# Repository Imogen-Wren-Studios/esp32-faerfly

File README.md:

#ESP32 FaerFly - Development Board
 Imogen Wren Business Card PCB

## Project Outline

_The project is a business card that can be handed out at gigs and work, and also a fun project to build!_

### Requirements
 1. A PCB business card I can hand out to people at gigs / work to advertise myself
 2. A fun electronics project or thing

### Idea

1. Mini pocket lightshow. Rechargable and interactive. Probably get it fabbed so it isnt a soldering project, but include a programming port so it can be reprogrammed easily. <br>
     **Advantages:**
    - Fun programming challenge - Can link to repo with working code in case of bricking
    - Card more likely to be used in the open and interacted with over time
    - Would have to be handed out with everything attached
    - Could exclude battery and make a point of indicating to reuse broken disposible vape for battery. Recycling electronic waste! 

 ## Strech Features
 
 - NFC Tap phone to link to linktree?
 - Edge connectors could be used as both touch interface, and connection to other hardware. Generic port? Is this now a new form we are trying to invent for development boards?
 - 3d printed case for different functions, like exposed touch pins, 

 ## Circuit Snippets
 
 ### WS2821b LED Implementation
 
  <br>
https://cdn-shop.adafruit.com/datasheets/WS2812B.pdf
- Vdd = 3.5 - 5.6 
- Vinput = VDD +-0.5

 Battery can be unregulated direct to LEDs & regulated to microcontroller
Slot for 2nd regulator for powering with 2s? or KISS

I think KISS

### Charging IC and LOw Voltage Cutoff

https://www.mouser.co.uk/ProductDetail/Littelfuse/SMAJ350A?

## Research

### AtTiny85 Interface
**DrAzzy - ATtiny Obsessee**
_Jan '20post #2_
_If you use my core (board manager url in sig), there is a serial bootloader (use the (optiboot) board def).
But you will still need an ISP programmer or arduino running Arduino as ISP sketch to bootload it (usbasps and nano clones are both 3 bucks or so on ebay/aliexpress, either is suitable).
You will also need a 0.1uf cap and 10k resistor for the autoreset circuit so the serial adapter can reset it into the bootloader. (Also, dont forget that you also need a 0.1uf ceramic cap between power and ground close to the t85 ti ensure reliable operation; without this the chip may behave erratically depending on circumstances - I mention this because it is very often omitted in designs I see here, particularly with tinies. You always need this for digital ICs unless otherwise specified in the datasheet. With the t85, if on breadboard or protoboard, i usually put this across the top of the chip to minimize the distance between cap and chip)_

#### USB - SPI Bridge

https://www.mouser.co.uk/ProductDetail/Microchip-Technology/MIC2550AYTS

#### USB C Connectors
https://www.mouser.co.uk/ProductDetail/Amphenol-Commercial-Products/124018402112A
https://www.lcsc.com/product-detail/span-style-background-color-ff0-USB-span-Connectors_G-Switch-GT-USB-7007A_C5299422.html

### LiPo Battery Charging
#### 1S
https://uk.rs-online.com/web/p/battery-management/7386360
https://www.mouser.co.uk/ProductDetail/Microchip-Technology-Atmel/MCP73832T-5ACI-OT
https://www.mouser.co.uk/datasheet/2/268/20001984g-846362.pdf

#### 2S
https://www.mouser.co.uk/ProductDetail/Microchip-Technology/MCP73844T-820I-MS

_This option needs regulator to 5v_

### Microcontroller Options
#### AtTiny85
- https://uk.farnell.com/microchip/attiny85-20su/mcu-8bit-attiny-20mhz-wsoic-8/dp/1455164
- Feels more "Haxxor" using a tiny processor
- More Difficult to implement
- The device achieves a throughput of 20 MIPS at 20 MHz and operates between 2.7 to 5.5V.
   - In voltage range 
- Have code almost ready to run https://github.com/Imogen-Wren-Studios/unicorn-attiny85

#### SAMD21
- 3.3v  MUST BE REGULATED
- Lots of experience with device
- https://www.mouser.co.uk/ProductDetail/Microchip-Technology/ATSAMD21E16L-AF?qs=9KdFJXLqUo%252B5fCZYsYcg9g%3D%3D

#### AtMega382p
- Most commonly understood platform - better engagement
- https://www.lcsc.com/product-detail/Microcontroller-Units-MCUs-MPUs-SOCs_Microchip-Tech-ATMEGA328P-AU_C14877.html
- Expensive
- in stock ATM
- 1.8 - 5.5v - No Need for Regulator
  - Qty.	Unit Price	Ext. Price
  - 1+	US  $3.045
  - 10+	US  $2.7126 - 	US$ 27.13

### ESP32
- 3v3 Only - needs regulating
- Wifiability gives further haxxor abilities
- OTA Updates
https://www.lcsc.com/product-detail/WiFi-Modules_Espressif-Systems-ESP32-WROOM-32-N4_C82899.html
- Have some code that could be used: https://github.com/Imogen-Wren-Studios/esp32-ws2812b-glediator
- Price: 
  - 1+   -  	US$3.2455	
  - 10+	 -   US$2.9273

### Capaciative Sensing

https://www.instructables.com/Capacitive-Sensing-for-Dummies/
_Seems to mostly be used with a microcontroller, havnt managed to find an analog audio implementation yet_

https://docs.arduino.cc/built-in-examples/analog/Smoothing Smoothing Data from Capacative touch sensor

## Continued Development

Now the project has become more clearly defined, it is an ESP development board with built in WS2821b LEDs designed to be used as a wearable badge, or a light up stand
for 3D printing projects. It contains mounting tabs to assit in adding diffusers and optics. The wifi can be used to coordinate groups of them to sync colours around the room.

## Version 2 Development

After using version 1 for a little time, some clear places to improve have materialised.

1.  [] Replace GPIO surface pins with through holes
2.  [] Replace USB to serial with CP2102, CH340 is too flakey see [CP2102 USB to UART](https://blackcatsoftware.us/wp-content/uploads/2020/06/esp32-devkit-v1-schematic.pdf)
3.  [] Add BMP280 temp sensor
4.  [] Add Accellerometer
5.  [] Add digital microphone? - test theory before committing
6.  [] DMX interface? -> `The DMX output required the use of a MAX485 transceiver connected to the TX-pin of the ESP in order to produce DMX output.` `If you need to use another pin for output than the TX-pin, you'll need to change this in the ESP-Dmx library itself. This setting is located in src/dependencies/dmx/ESPDMX.cpp on line 31.`
7.  [x] Battery Positive to ADC1 (GPIO32-39) with 100k resistor for battery usermod
8.  [x] Change Battery Switch to switch between USB and battery (why didnt do this on version 1?!?!)
9.  [x] Check max charge current for BMS. Need at least 1A if possible 550mA max using 2k ohm shunt resistor

Does DMX make this project something it is not?

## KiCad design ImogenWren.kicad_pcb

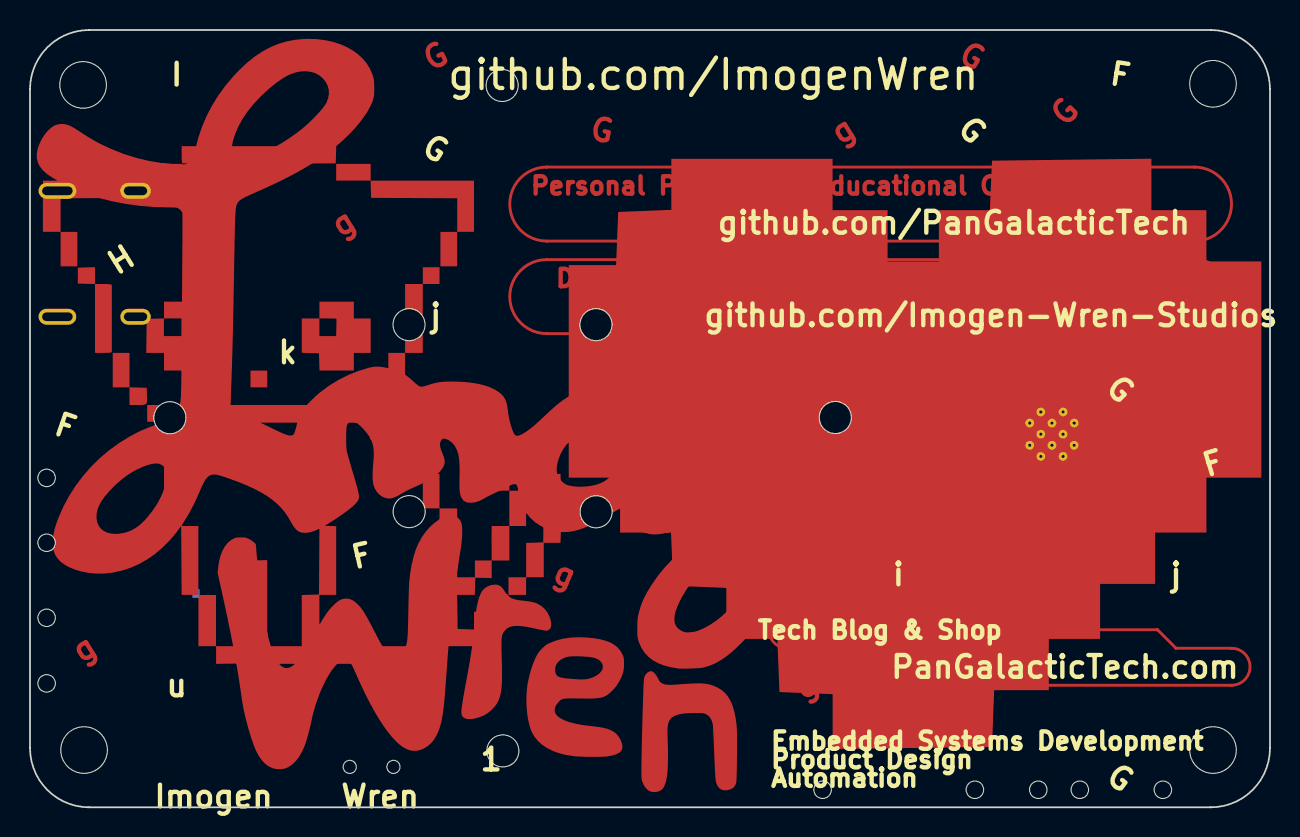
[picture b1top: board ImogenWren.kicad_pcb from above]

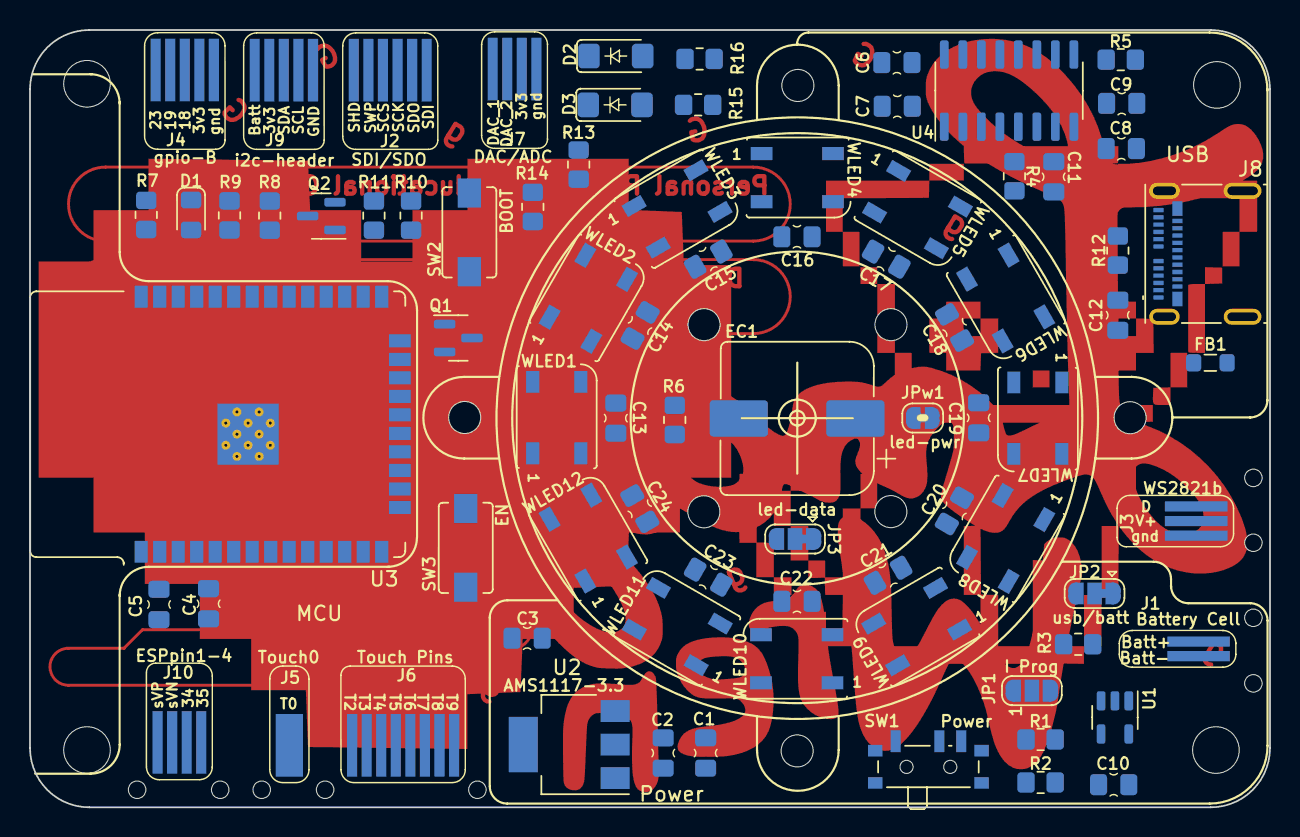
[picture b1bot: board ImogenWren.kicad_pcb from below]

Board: 2 copper layers, 85.1 x 53.3 mm, 80 parts (80 on the bottom side), 73 nets, no tracks yet.

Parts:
C1, C2, C3, C4, C5, C6, C7, C10, C13, C14, C15, C16, C17, C18, C19, C20, C21, C22, C23, C24: 100n; C_0805_2012_HandSolder_kawaii
C8: 10n; C_0805_2012_HandSolder_kawaii
C9, C11: 47p; C_0805_2012_HandSolder_kawaii
C12: 4n7; C_0805_2012_HandSolder_kawaii
D1: Blue; LED_0805_2012_Kawaii
D2, D3: BZV55B3V3; D_MiniMELF_kawaii
EC1: 1000u; CP_Elec_10x10_kawaii
FB1: FerriteBead; L_0805_2012Metric_Pad1.05x1.20mm_HandSolder
J1: Battery Cell; 2-pin-edge
J2: SDI/SDO; 6-pin-edge-touch
J3: WS2821b; 3-pin-edge
J4: gpio-B; 5-pin-edge-touch
J5: Touch0; 1-pin-edge-touch-xl
J6: Touch Pins; 8-pin-edge-touch
J7: DAC/ADC; 4-pin-edge
J8: USB_C_Receptacle; USB_C_Receptacle_Molex_105450-0101
J9: i2c-header; 5-pin-edge-touch
J10: ESPpin1-4; 4-pin-edge
JP1: I Prog; SolderJumper-3_P1.3mm_Open_RoundedPad1.0x1.5mm_NumberLabels
JP2: usb/batt; SolderJumper-3_P1.3mm_Bridged12_RoundedPad1.0x1.5mm
JP3: led-data; SolderJumper-3_P1.3mm_Bridged12_RoundedPad1.0x1.5mm
JPw1: led-pwr; SolderJumper-2_P1.3mm_Bridged_RoundedPad1.0x1.5mm
Q1, Q2: BC817; SOT-23
R1, R2, R8, R9, R10, R11: 10k; R_0805_2012Metric_Pad1.20x1.40mm_HandSolder
R3: 4k7; R_0805_2012Metric_Pad1.20x1.40mm_HandSolder
R4, R5: 27r; R_0805_2012Metric_Pad1.20x1.40mm_HandSolder
R6: 470r; R_0805_2012Metric_Pad1.20x1.40mm_HandSolder
R7: 330r; R_0805_2012Metric_Pad1.20x1.40mm_HandSolder
R12: 5k2; R_0805_2012Metric_Pad1.20x1.40mm_HandSolder
R13, R14: 220r; R_0805_2012Metric_Pad1.20x1.40mm_HandSolder
R15, R16: 100r; R_0805_2012Metric_Pad1.20x1.40mm_HandSolder
SW1: SW_SPDT_small; SW_SPDT_PCM12
SW2: BOOT; SW_SPST_EVQPE1
SW3: EN; SW_SPST_EVQPE1
U1: MCP73831-2-OT; SOT-23-5
U2: AMS1117-3.3; SOT-223-3_TabPin2
U3: ESP32-WROOM-32; ESP32-WROOM-32_KAWAII
U4: CH340C; SOIC-16_3.9x9.9mm_P1.27mm
WLED1, WLED2, WLED3, WLED4, WLED5, WLED6, WLED7, WLED8, WLED9, WLED10, WLED11, WLED12: WS2812B; LED_WS2812B_PLCC4_5.0x5.0mm_P3.2mm

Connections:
18: J4.A3, U3.30 (GPIO18)
19: J4.A4, U3.31 (GPIO19)
23: D1.2 (A), J4.A5, U3.37 (GPIO23)
/BATTERY_POWER: JP2.1 (A), SW1.1 (A), U1.3 (V_{BAT})
/BATTERY_POWER_BUS: C1.1, C2.1, EC1.1, J3.A2, J9.A5, JP2.2 (C), JPw1.1 (A), U2.3 (VI)
/CHARGE_INHIBIT: R1.1, R2.1, R3.1, U1.5 (PROG)
/ESP32/3V3_BUS: C3.1, C5.1, J4.A2, J7.A2, J9.A4, R8.1, R9.1, U2.2 (VO), U3.2 (VDD)
/ESP32/D+: R5.1, U4.5 (UD+)
/ESP32/D-: R4.1, U4.6 (UD-)
/ESP32/LED_DATA_OUT: R6.2, U3.29 (GPIO5)
/ESP32/MCU_5V_BUS: C6.1, U4.16 (VCC)
/ESP32/USB ESP32 CH340 Interface /ESP_EN: C4.1, Q2.3 (C), SW3.1, U3.3 (EN)
/ESP32/USB ESP32 CH340 Interface /ESP_IO0: Q1.3 (C), SW2.1, U3.25 (IO0/GPIO0/T1)
/ESP32/USB ESP32 CH340 Interface /RxD_B: U3.35 (TXD0/GPIO1), U4.3 (RXD)
/ESP32/USB ESP32 CH340 Interface /TxD_B: U3.34 (RXD0/GPIO3), U4.2 (TXD)
/USB/D+: C9.1, J8.A6 (D+), J8.B6 (D+), R5.2
/USB/D-: C11.1, J8.A7 (D-), J8.B7 (D-), R4.2
/USB_POWER: C10.1, C12.1, FB1.2, JP2.3 (B), U1.4 (V_{DD})
/WS2812b LEDs/5V_IN: C13.1, C14.1, C15.1, C16.1, C17.1, C18.1, C19.1, C20.1, C21.1, C22.1, C23.1, C24.1, JPw1.2 (B), WLED1.1 (VDD), WLED2.1 (VDD), WLED3.1 (VDD), WLED4.1 (VDD), WLED5.1 (VDD), WLED6.1 (VDD), WLED7.1 (VDD), WLED8.1 (VDD), WLED9.1 (VDD), WLED10.1 (VDD), WLED11.1 (VDD), WLED12.1 (VDD)
/WS2812b LEDs/DATA_IN: JP3.1 (A), R6.1, WLED1.4 (DIN)
/WS2812b LEDs/DATA_OUT: JP3.3 (B), WLED12.2 (DOUT)
GND: C1.2, C2.2, C3.2, C4.2, C5.2, C6.2, C7.2, C13.2, C14.2, C15.2, C16.2, C17.2, C18.2, C19.2, C20.2, C21.2, C22.2, C23.2, C24.2, EC1.2, J3.A1, J4.A1, J7.A1, J9.A1, R7.2, R15.1, R16.1, SW2.2, SW3.2, U2.1 (GND), U3.1 (GND), U3.15 (GND), U3.38 (GND), U3.39 (GND), U4.1 (GND), WLED1.3 (VSS), WLED2.3 (VSS), WLED3.3 (VSS), WLED4.3 (VSS), WLED5.3 (VSS), WLED6.3 (VSS), WLED7.3 (VSS), WLED8.3 (VSS), WLED9.3 (VSS), WLED10.3 (VSS), WLED11.3 (VSS), WLED12.3 (VSS)
GNDPWR: C8.2, C9.2, C10.2, C11.2, C12.2, J1.A1, J8.A1 (GND), J8.A12 (GND), J8.B1 (GND), J8.B12 (GND), J8.S1 (SHIELD), JP1.2 (C), R1.2, R12.1, U1.2 (V_{SS})
unnamed: C8.1, FB1.1, J8.A4 (VBUS), J8.A9 (VBUS), J8.B4 (VBUS), J8.B9 (VBUS)
unnamed: D1.1 (K), R7.1
unnamed: D2.2 (A), R16.2
unnamed: D2.1 (K), J7.A3, R14.1
unnamed: D3.2 (A), R15.2
unnamed: D3.1 (K), J7.A4, R13.1
unnamed: J8.A5 (CC1), R12.2
unnamed: JP1.1 (A), R2.2
unnamed: JP1.3 (B), R3.2
unnamed: J3.A3, JP3.2 (C)
unnamed: Q1.1 (B), R10.2
unnamed: Q1.2 (E), R11.1, U4.13 (~DTR)
unnamed: Q2.1 (B), R11.2
unnamed: Q2.2 (E), R10.1, U4.14 (~RTS)
unnamed: J1.A2, SW1.2 (B)
unnamed: J6.A1, U3.24 (GPIO2(T2))
unnamed: J5.A1, U3.26 (GPIO4(T0))
unnamed: J6.A4, U3.14 (GPIO12(T5))
unnamed: J6.A3, U3.16 (GPIO13(T4))
unnamed: J6.A5, U3.13 (GPIO14(T6))
unnamed: J6.A2, U3.23 (GPIO15(T3))
unnamed: R13.2, U3.10 (GPIO25(DAC_1))
unnamed: R14.2, U3.11 (GPIO26(DAC_2))
unnamed: J6.A6, U3.12 (GPIO27(T7))
unnamed: J6.A8, U3.8 (GPIO32(T9))
unnamed: J6.A7, U3.9 (GPIO33(T8))
unnamed: J10.A3, U3.6 (IO34)
unnamed: J10.A4, U3.7 (IO35)
unnamed: J2.A3, U3.20 (SCK/CLK)
unnamed: J2.A4, U3.19 (SCS/CMD)
unnamed: J2.A1, U3.22 (SDI/SD1)
unnamed: J2.A2, U3.21 (SDO/SD0)
unnamed: J10.A2, U3.5 (SENSOR_VN)
unnamed: J10.A1, U3.4 (SENSOR_VP)
unnamed: J2.A6, U3.17 (SHD/SD2)
unnamed: J2.A5, U3.18 (SWP/SD3)
unnamed: C7.1, U4.4 (V3)
unnamed: WLED1.2 (DOUT), WLED2.4 (DIN)
unnamed: WLED2.2 (DOUT), WLED3.4 (DIN)
unnamed: WLED3.2 (DOUT), WLED4.4 (DIN)
unnamed: WLED4.2 (DOUT), WLED5.4 (DIN)
unnamed: WLED5.2 (DOUT), WLED6.4 (DIN)
unnamed: WLED6.2 (DOUT), WLED7.4 (DIN)
unnamed: WLED7.2 (DOUT), WLED8.4 (DIN)
unnamed: WLED8.2 (DOUT), WLED9.4 (DIN)
unnamed: WLED9.2 (DOUT), WLED10.4 (DIN)
unnamed: WLED10.2 (DOUT), WLED11.4 (DIN)
unnamed: WLED11.2 (DOUT), WLED12.4 (DIN)
SCL: J9.A2, R8.2, U3.36 (GPIO22)
SDA: J9.A3, R9.2, U3.33 (GPIO21)

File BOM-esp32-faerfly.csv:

#,Reference,Qty,Value,Footprint,DNP,JLCpart,Cost
1,"C1, C2, C3, C4, C5, C6, C7, C10, C13, C14, C15, C16, C17, C18, C19, C20, C21, C22, C23, C24",20,100n,000_Capacitors_Immo:C_0805_2012_HandSolder_kawaii,,C779975,0.02
2,C8,1,10n,000_Capacitors_Immo:C_0805_2012_HandSolder_kawaii,,C83170,0.0051
3,"C9, C11",2,47p,000_Capacitors_Immo:C_0805_2012_HandSolder_kawaii,,C24659,0.0056
4,C12,1,4n7,000_Capacitors_Immo:C_0805_2012_HandSolder_kawaii,,C2915753,0.0118
5,"C25, C26",2,4u7,Capacitor_Tantalum_SMD:CP_EIA-2012-12_Kemet-R_Pad1.30x1.05mm_HandSolder,,C1954175,0.0994
6,D1,1,Blue,Diode_SMD:D_0805_2012Metric_Pad1.15x1.40mm_HandSolder,,C84261,0.0158
7,"D2, D3",2,BZV55B3V3,Diode_SMD:D_MiniMELF,,C268735,0.0221
8,EC1,1,1000u,Capacitor_SMD:CP_Elec_10x10,,C134726,0.1866
9,FB1,1,FerriteBead,Inductor_SMD:L_0805_2012Metric_Pad1.05x1.20mm_HandSolder,,C845115,0.558
10,J8,1,USB_C_Receptacle,Connector_USB:USB_C_Receptacle_Molex_105450-0101,,C134092,0.6619
12,"Q1, Q2",2,BC817,Package_TO_SOT_SMD:SOT-23,,C2137,0.0225
13,"R1, R2, R8, R9, R10, R11",6,10k,Resistor_SMD:R_0805_2012Metric_Pad1.20x1.40mm_HandSolder,,C2930231,0.002
14,"R3, R12",2,4k7,Resistor_SMD:R_0805_2012Metric_Pad1.20x1.40mm_HandSolder,,C5140142,0.002
15,"R4, R5",2,27r,Resistor_SMD:R_0805_2012Metric_Pad1.20x1.40mm_HandSolder,,C779975,0.002
16,R6,1,470r,Resistor_SMD:R_0805_2012Metric_Pad1.20x1.40mm_HandSolder,,C280020,0.0027
17,R7,1,330r,Resistor_SMD:R_0805_2012Metric_Pad1.20x1.40mm_HandSolder,,C3017834,0.0016
18,"R13, R14, R17",3,1k,Resistor_SMD:R_0805_2012Metric_Pad1.20x1.40mm_HandSolder,,C218388,0.0082
19,"R15, R16",2,100r,Resistor_SMD:R_0805_2012Metric_Pad1.20x1.40mm_HandSolder,,C217766,0.0093
20,SW1,1,SW_SPDT_small,000_Switches_Immo:SW_SPDT_PCM12,,C221841,0.4487
21,SW2,1,BOOT,000_Switches_Immo:SW_SPST_EVQPE1,,C699451,0.3052
22,SW3,1,EN,000_Switches_Immo:SW_SPST_EVQPE1,,C699451,0.3052
23,U1,1,MCP73831-2-OT,Package_TO_SOT_SMD:SOT-23-5,,C424093,0.778
24,U2,1,AMS1117-3.3,Package_TO_SOT_SMD:SOT-223-3_TabPin2,,C2992570,0.0488
25,U3,1,ESP32-WROOM-32,RF_Module:ESP32-WROOM-32,,C473012 - C529577,3.5016
26,U4,1,CH340C,Package_SO:SOIC-16_3.9x9.9mm_P1.27mm,,C84681,0.4725
27,"WLED1, WLED2, WLED3, WLED4, WLED5, WLED6, WLED7, WLED8, WLED9, WLED10, WLED11, WLED12",12,WS2812B,LED_SMD:LED_WS2812B_PLCC4_5.0x5.0mm_P3.2mm,,C2920042,0.0768

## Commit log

2023-02-05 thgdftg
2023-02-06 added files
2023-02-15 cvcvb
2023-02-16 finished front design V1, next do circuit
2023-02-16 Moved Fuzz Files to FlyingFoxFuzz
2023-02-17 Lots of Developments
2023-02-18 dfghdreg
2023-02-18 dhdfbg
2023-02-18 nvbghnv bn
2023-02-23 sdfdsfvsd
2023-02-26 n;kln;sfdg
2023-02-28 werewr
2023-02-28 kjsaofklihsdof
2023-03-02 ;j;lkjh;k
2023-03-03 erwterge
2023-03-03 xcfgdfgd
2023-03-03 desgfdfg
2023-03-04 dfhdyhdre
2023-03-05 [drtydf
2023-03-06 DSGFDSF
2023-03-08 cgfhfhfg
2023-03-09 34terg
2023-03-10 Named Lumino for now
2023-03-10 erytr
2023-03-10 Got to Routing. Keeps crashing on me
2023-03-11 Started routing board but keeps crashing
2023-03-13 Recoverd
2023-03-13 dfbgdfg
2023-03-14 Updated Schematic for Battery Charge Sense + read datasheet for battery charger IC
2023-03-15 raeojigerge
2023-03-16 gfjgfhjrtgf
2023-03-16 nearly there
2023-03-16 sertergrer
2023-03-17 dslghdkjsg
2023-03-18 finished design V1
2023-03-18 wsdfsdfs
2023-03-19 added kawaii font
2023-03-19 V1.1 Design Finished
2023-03-19 regerge
2023-03-21 Adding BOM
2023-03-21 437543756
2023-03-22 fswegfewf
2023-03-22 dfghdfh
2023-03-23 dsfgdsfgd
2023-03-23 Reorganised and renamed files
2023-03-23 moved folders
2023-03-23 added JLC part numbers
2023-03-24 Added Complete BOM
    Ready for Parts Shopping!
2023-03-24 fgndfbf
2023-03-24 updated BOM
2023-03-26 dfgdfg
2023-03-26 started working on statemachine for RTOS
2023-03-28 added state machine task to free rtos
2023-03-28 qwerwerw
2023-04-02 sdvsdfgsd
2023-04-02 aaahhh have no idea why multiple copies of library are included when only one reference to them
2023-04-03 \aahhhhhHH
2023-04-03 sdfsdfsdf
2023-04-18 kfkghfk
2023-04-18 cgfhnjgfyhj
2023-04-19 drehfrtyhrtf
2023-04-23 Revert "drehfrtyhrtf"
    This reverts commit bbe24f7e50a287e427fac67166e0b6a4a3b8b683.
2023-04-23 Added very basic test for esp32-faerfly board. Confirmed working but needs pin change
2023-04-25 added more firmware and 3D step file
2023-04-26 ,hljkhl
2023-04-26 Latest Broken update
2023-04-26 zips
2023-04-26 Fixed compilation issue
    #TODO: Slow down animation speed it is far too fast!
2023-04-26 Animations finally LOOK GOOD! random palettes looks crispy and sharp
    Now is just to tie methods into a clear and neat API for choosing colours and animation speed, steps between colours etc.
2023-04-27 tidied up operation slightly.
2023-04-27 update to firmware
2023-04-27 added 3D CAD for case design
2023-04-27 Added 3D case designs
2023-04-27 3D cad stuff
2023-04-28 3D CAD changed to version 2, version 1 accidently overwritten in process
2023-04-28 added battery holder
2023-04-29 Organised 3D cad folder
    Version B is latest version of case - hopefully last but still printing
2023-04-29 Added working demo firmware. unicornObject library is considered unstable
2023-04-30 addded intro animation
2023-04-30 cftfkyfk
2023-05-01 ihljhkjhg
2023-05-03 maybe be ready to roll this one back
    trying to upload to ESP32 seems to have bricked device :(
2023-05-08 Started working on V2.0 PCB
2023-05-08 started adding modifcations for V2 see changelog
2023-05-09 expanded unicorn library functionality
2023-05-09 major updates to unicorn library
    - Now prints the colours picked
    - random palette picker working
    - pride palette array working.
    - Understand a little more about how the passed values play together to change the effect
    - added description for the different timing parts.
2023-05-09 little update
2023-05-10 added planet palettes to unicornObject
2023-05-11 major firmware update. Now introduced effects to unicorn library
    effects change how palettes are applied to LEDs
2023-05-11 added suggestions for improvements
2023-05-11 fuckin with stuff
2023-05-14 some updates to firmjware not as neat as would like
2023-05-16 Updates to V2.0 PCB
2023-06-04 jkhgjkytkl
2023-06-08 added i2c mic test firmware
2025-01-22 nkjh
2025-01-22 update to new version
